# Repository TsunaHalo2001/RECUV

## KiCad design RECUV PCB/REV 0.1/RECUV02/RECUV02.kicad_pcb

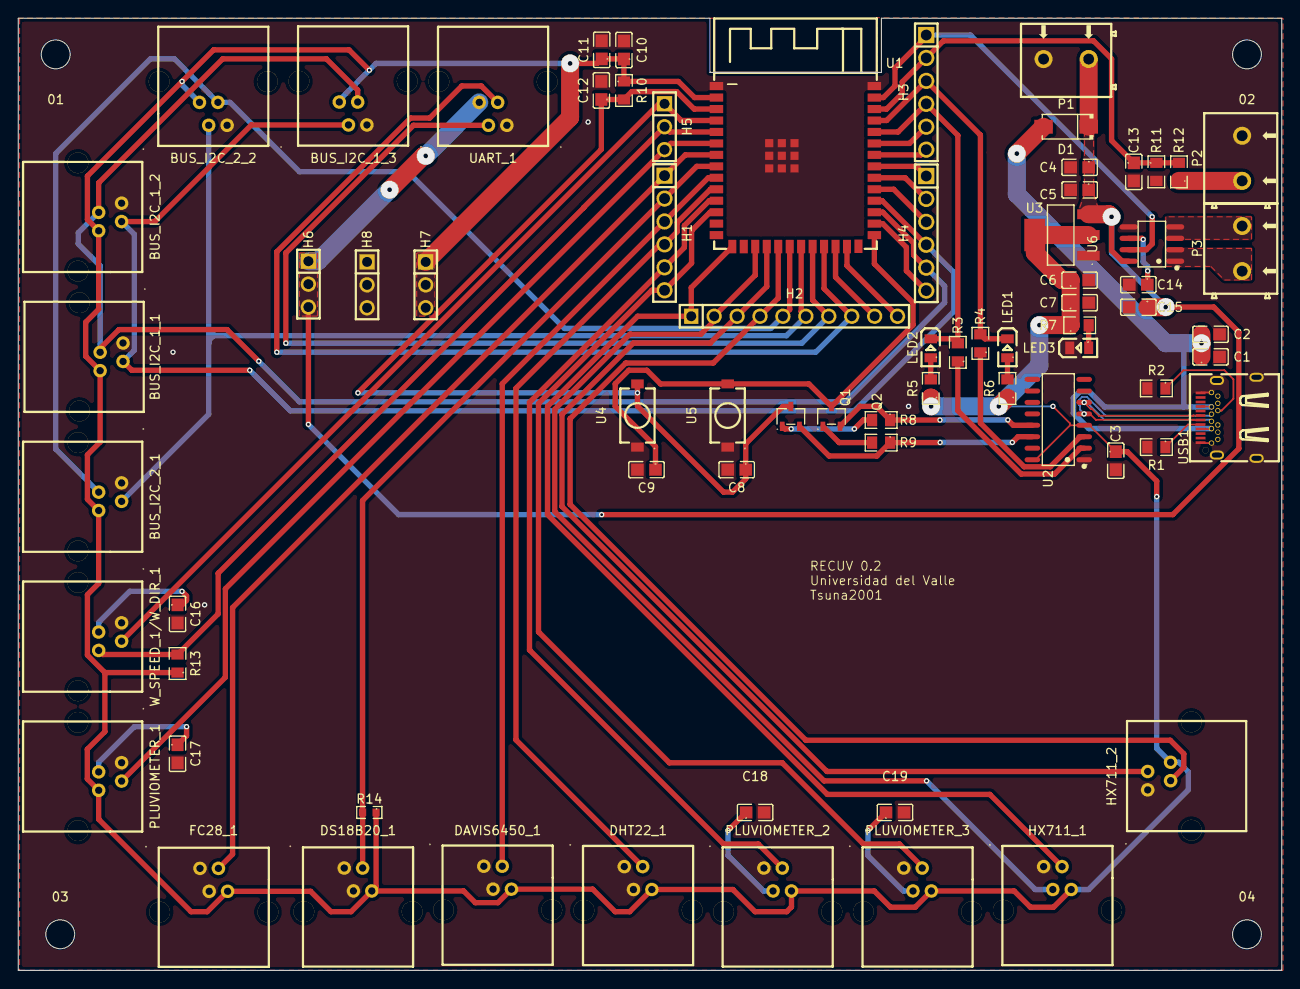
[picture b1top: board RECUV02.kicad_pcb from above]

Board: 2 copper layers, 140.0 x 105.5 mm, 77 parts (0 on the bottom side), 58 nets.

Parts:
01, 02, 03, 04: MountingHole_3.2mm_M3
BUS_I2C_1_1, BUS_I2C_2_1: TSL2591; RJ11-TH_PCB-6P4C-90
BUS_I2C_1_2: PRES_ATMOS; RJ11-TH_PCB-6P4C-90
BUS_I2C_1_3, BUS_I2C_2_2: EXTENDER; RJ11-TH_PCB-6P4C-90
C1, C5, C6, C10: 10u; C0805
C2, C3, C4, C7, C8, C9, C11, C13, C15, C16, C17, C18, C19: 100n; C0805
C12: 1u; C0805
C14: 1n; C0805
D1: SS54_C22452; SMA_L4.4-W2.8-LS5.4-R-RD
DAVIS6450_1: SOLAR_RADIATION; RJ11-TH_PCB-6P4C-90
DHT22_1: AIR_HUMIDITY/AIR_TEMPERATURE; RJ11-TH_PCB-6P4C-90
DS18B20_1: TEMP_SOIL; RJ11-TH_PCB-6P4C-90
FC28_1: HUMIDITY_SOIL; RJ11-TH_PCB-6P4C-90
H1: LEFT_ROW_2; HDR-TH_6P-P2.54-V-M-1
H2: LOW_ROW; HDR-TH_10P-P2.54-V-M-1
H3: RIGHT_ROW_1; HDR-TH_6P-P2.54-V-M-1
H4: RIGHT_ROW_2; HDR-TH_6P-P2.54-V-M-1
H5: LEFT_ROW_1; HDR-TH_3P-P2.54-V-M
H6: 5V_ROW; HDR-TH_3P-P2.54-V-M
H7: 3V3_ROW; HDR-TH_3P-P2.54-V-M
H8: GND_ROW; HDR-TH_3P-P2.54-V-M
HX711_1, HX711_2: NET_WEIGHT; RJ11-TH_PCB-6P4C-90
LED1: Green; LED0805-R-RD
LED2: Blue; LED0805-R-RD
LED3: Red; LED0805-R-RD
P1: VEXT; CONN-TH_2P-P5.00_CPC3703CTR
P2: VOLTAGE; CONN-TH_2P-P5.00_CPC3703CTR
P3: CURRENT; CONN-TH_2P-P5.00_CPC3703CTR
PLUVIOMETER_1, PLUVIOMETER_2, PLUVIOMETER_3: PLUVIOMETER; RJ11-TH_PCB-6P4C-90
Q1, Q2: MMBT2222ALT1; SOT-23-3_L3.0-W1.7-P0.95-LS2.9-BR
R1, R2: 5.1k; R0805
R3, R4: 1k; R0805
R5, R6, R7: 470; R0805
R8, R9, R10, R11, R13: 10k; R0805
R12: 100k; R0805
R14: 2.2k; R0603
U1: ESP32-S3-WROOM-1; WIRELM-SMD_ESP32-S3-WROOM-1
U2: CH340C; SOP-16_L10.0-W3.9-P1.27-LS6.0-BL
U3: A1117-3.3; SOT-223-3_L6.5-W3.4-P2.30-LS7.0-BR-1
U4: RESET; SW-SMD_KSR213GLFG
U5: BOOT; SW-SMD_KSR213GLFG
U6: ACS712ELCTR-20A-T; SOIC-8_L4.9-W3.9-P1.27-LS6.0-BL
UART_1: COMMUNICATION; RJ11-TH_PCB-6P4C-90
USB1: USB-306; USB-TYPE-C-TH_USB-306-1
W_SPEED_1/W_DIR_1: WIND; RJ11-TH_PCB-6P4C-90

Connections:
3V3: BUS_I2C_1_1.4, BUS_I2C_1_2.4, BUS_I2C_1_3.4, BUS_I2C_2_1.4, BUS_I2C_2_2.4, C3.1, C6.1, C7.1, C10.1, C11.1, DAVIS6450_1.4, DHT22_1.4, DS18B20_1.4, FC28_1.4, H7.1, H7.2, H7.3, HX711_1.4, HX711_2.4, PLUVIOMETER_1.4, PLUVIOMETER_2.4, PLUVIOMETER_3.4, R5.1, R6.1, R7.1, R10.1, R13.1, R14.1, U1.2 (3V3), U2.4 (V3), U2.16 (VCC), U3.2 (VOUT)
+5V: C4.1, C5.1, C15.1, D1.2 (K), H6.1, H6.2, H6.3, P1.1, U3.3 (VIN), U6.8 (VCC), UART_1.4
CHIP_PU: C8.1, C12.1, Q1.3 (C), R10.2, U1.3 (EN), U4.2
DTR: Q2.2 (E), R8.1, U2.13 (~DTR)
GND: BUS_I2C_1_1.1, BUS_I2C_1_2.1, BUS_I2C_1_3.1, BUS_I2C_2_1.1, BUS_I2C_2_2.1, C1.2, C2.2, C3.2, C4.2, C5.2, C6.2, C7.2, C8.2, C9.2, C10.2, C11.2, C12.2, C13.2, C14.2, C15.2, C16.2, C17.2, C18.2, C19.2, DAVIS6450_1.1, DAVIS6450_1.2, DHT22_1.1, DHT22_1.2, DS18B20_1.1, DS18B20_1.2, FC28_1.1, FC28_1.2, H8.1, H8.2, H8.3, HX711_1.1, HX711_2.1, LED3.2 (K), P1.2, P2.2, PLUVIOMETER_1.1, PLUVIOMETER_2.1, PLUVIOMETER_3.1, R1.2, R2.2, R11.2, U1.1 (GND), U1.40 (GND), U1.41 (GND), U2.1 (GND), U3.1 (ADJ/GND), U4.1, U5.1, U6.5 (GND), UART_1.1, USB1.25 (EH), USB1.A1 (GND), USB1.A12 (GND), USB1.B1 (GND), USB1.B12 (GND), W_SPEED_1/W_DIR_1.1
GPIO00: C9.1, Q2.3 (C), U1.27 (IO0), U5.2
GPIO01: H3.1, U1.39 (IO1), U6.7 (VIOUT)
GPIO02: C13.1, H3.2, R11.1, R12.2, U1.38 (IO2)
GPIO03: H2.1, HX711_1.3, U1.15 (IO3)
GPIO04: H5.1, U1.4 (IO4), W_SPEED_1/W_DIR_1.3
GPIO05: H5.2, R13.2, U1.5 (IO5), W_SPEED_1/W_DIR_1.4
GPIO06: H5.3, PLUVIOMETER_1.3, U1.6 (IO6)
GPIO07: FC28_1.3, H1.1, U1.7 (IO7)
GPIO08: H1.6, PLUVIOMETER_3.3, U1.12 (IO8)
GPIO09: H2.2, HX711_1.2, U1.17 (IO9)
GPIO10: H2.3, HX711_2.3, U1.18 (IO10)
GPIO11: H2.4, HX711_2.2, U1.19 (IO11)
GPIO12: BUS_I2C_2_1.2, BUS_I2C_2_2.2, H2.5, U1.20 (IO12)
GPIO13: BUS_I2C_2_1.3, BUS_I2C_2_2.3, H2.6, U1.21 (IO13)
GPIO14: H2.7, U1.22 (IO14), UART_1.3
GPIO15: DS18B20_1.3, H1.2, R14.2, U1.8 (IO15)
GPIO16: DAVIS6450_1.3, H1.3, U1.9 (IO16)
GPIO17: DHT22_1.3, H1.4, U1.10 (IO17)
GPIO18: H1.5, PLUVIOMETER_2.3, U1.11 (IO18)
GPIO21: H2.8, U1.23 (IO21), UART_1.2
GPIO35: H4.6, U1.28 (IO35)
GPIO36: BUS_I2C_1_1.2, BUS_I2C_1_2.2, BUS_I2C_1_3.2, H4.5, U1.29 (IO36)
GPIO37: BUS_I2C_1_1.3, BUS_I2C_1_2.3, BUS_I2C_1_3.3, H4.4, U1.30 (IO37)
GPIO38: H4.3, U1.31 (IO38)
GPIO39: H4.2, U1.32 (IO39)
GPIO40: H4.1, U1.33 (IO40)
GPIO41: H3.6, U1.34 (IO41)
GPIO42: H3.5, U1.35 (IO42)
GPIO47: H2.9, U1.24 (IO47)
GPIO48: H2.10, U1.25 (IO48)
unnamed: C16.1, W_SPEED_1/W_DIR_1.2
unnamed: C17.1, PLUVIOMETER_1.2
unnamed: C18.1, PLUVIOMETER_2.2
unnamed: C19.1, PLUVIOMETER_3.2
unnamed: LED1.1 (A), R6.2
unnamed: LED2.1 (A), R5.2
unnamed: LED3.1 (A), R7.2
unnamed: P3.1, U6.1 (IP+), U6.2 (IP+)
unnamed: P3.2, U6.3 (IP-), U6.4 (IP-)
unnamed: Q1.1 (B), R8.2
unnamed: Q2.1 (B), R9.2
unnamed: R4.1, U2.3 (RXD)
unnamed: R3.1, U2.2 (TXD)
unnamed: C14.1, U6.6 (FILTER)
unnamed: R1.1, USB1.A5 (CC1)
unnamed: R2.1, USB1.B5 (CC2)
RTS: Q1.2 (E), R9.1, U2.14 (~RTS)
U0RXD: H3.4, LED2.2 (K), R3.2, U1.36 (RXD0)
U0TXD: H3.3, LED1.2 (K), R4.2, U1.37 (TXD0)
UD+: U2.5 (D+), USB1.A6 (DP1), USB1.B6 (DP2)
UD-: U2.6 (D-), USB1.A7 (DN1), USB1.B7 (DN2)
VBAT: P2.1, R12.1
VBUS: C1.1, C2.1, D1.1 (A), USB1.A4 (VBUS), USB1.A9 (VBUS), USB1.B4 (VBUS), USB1.B9 (VBUS)

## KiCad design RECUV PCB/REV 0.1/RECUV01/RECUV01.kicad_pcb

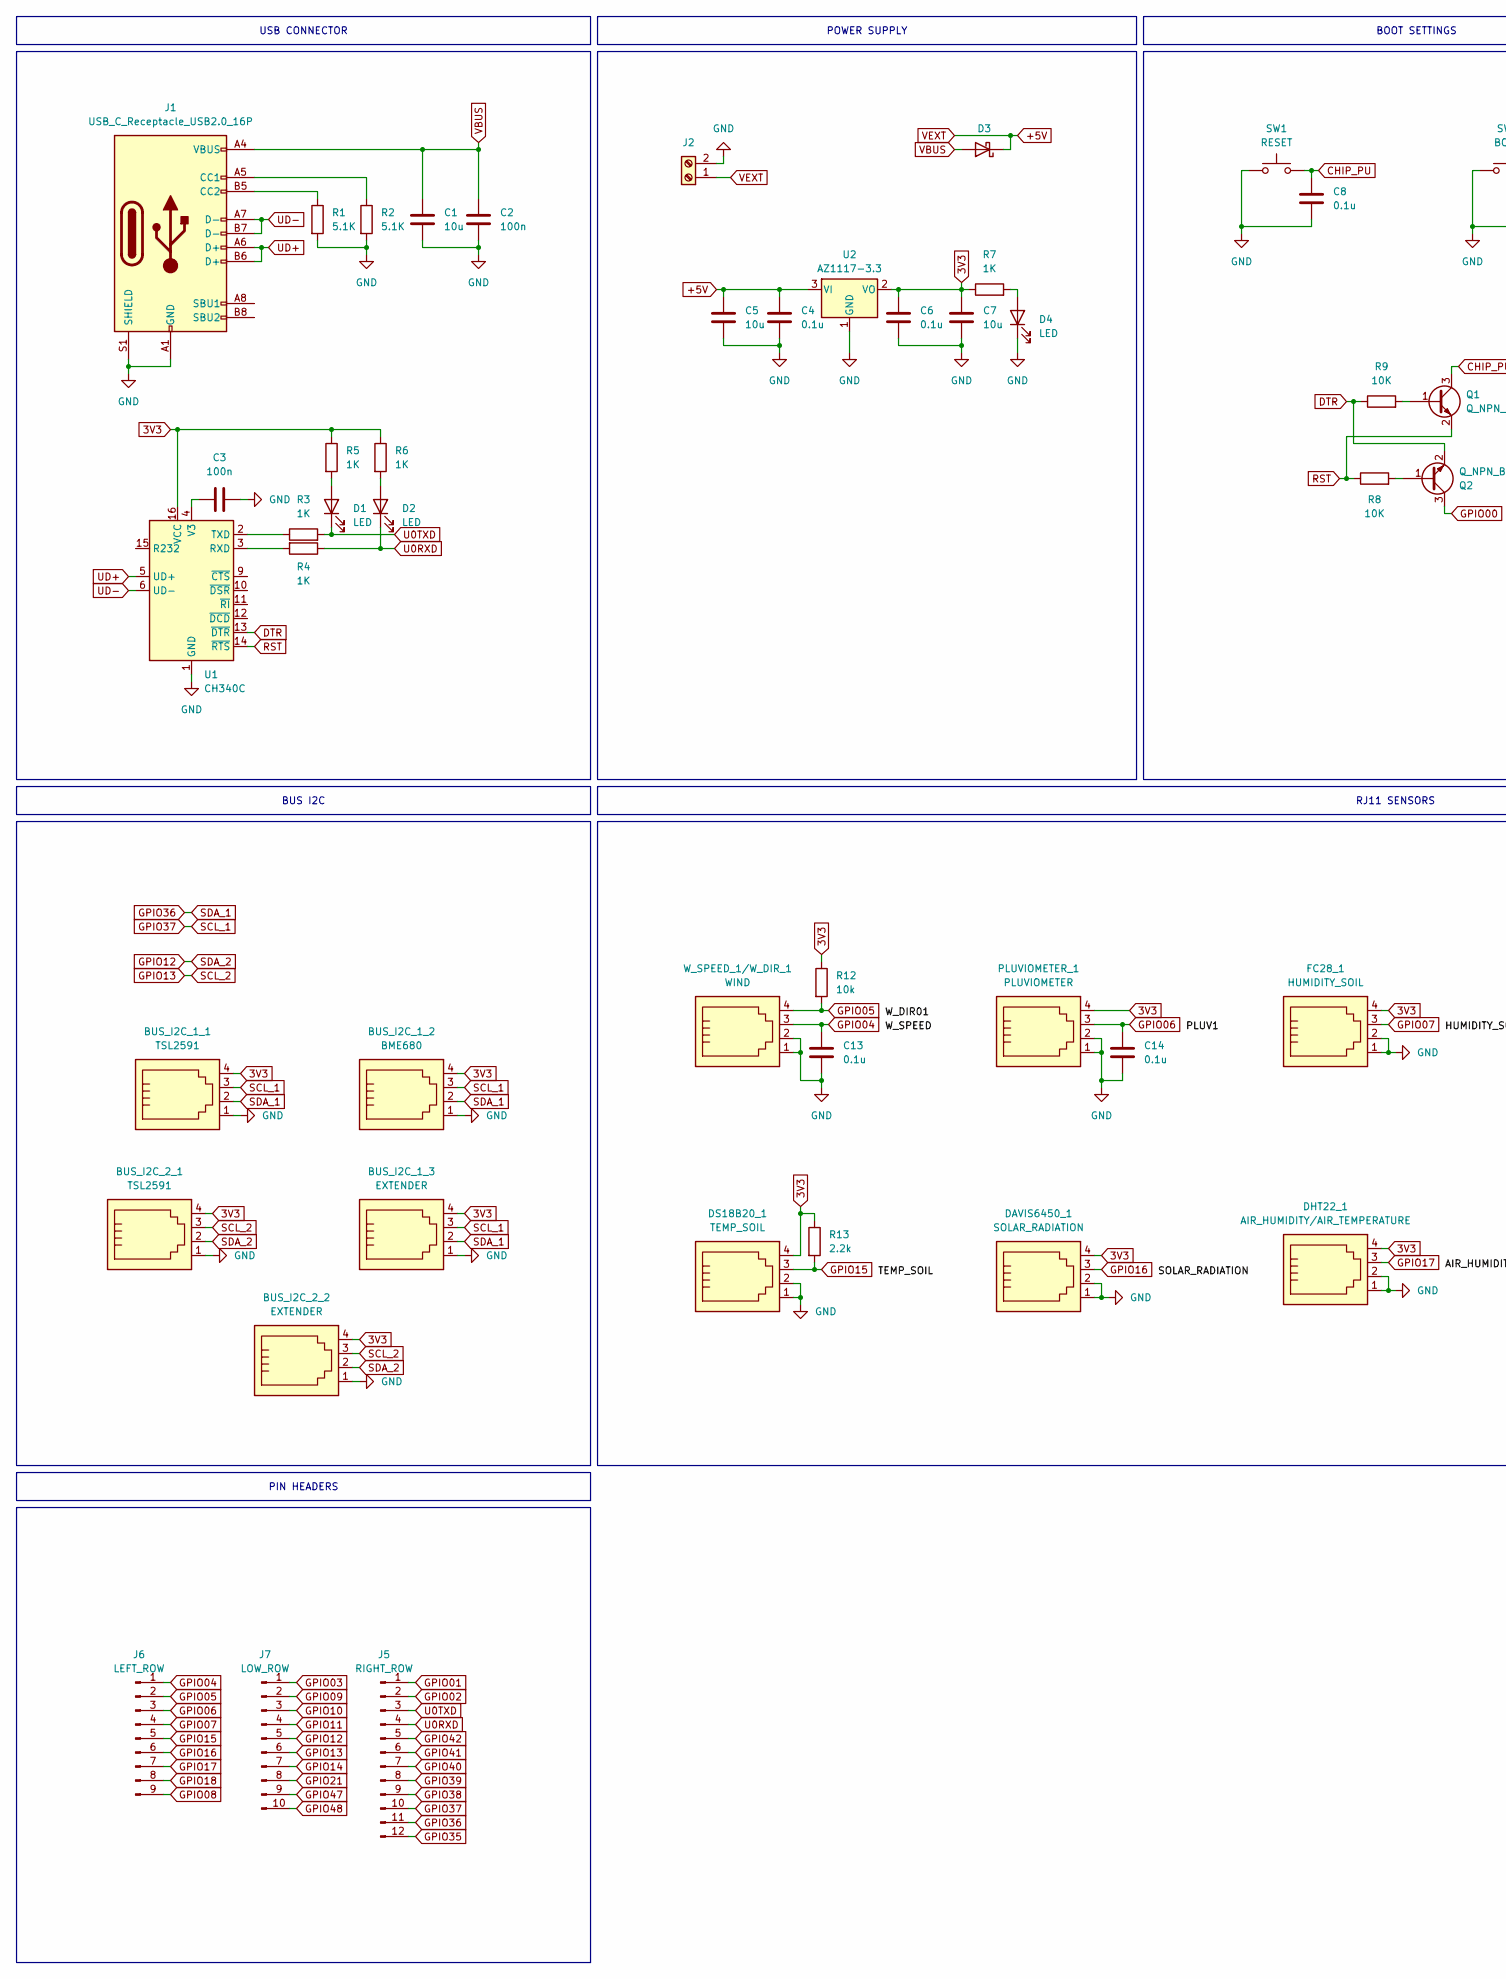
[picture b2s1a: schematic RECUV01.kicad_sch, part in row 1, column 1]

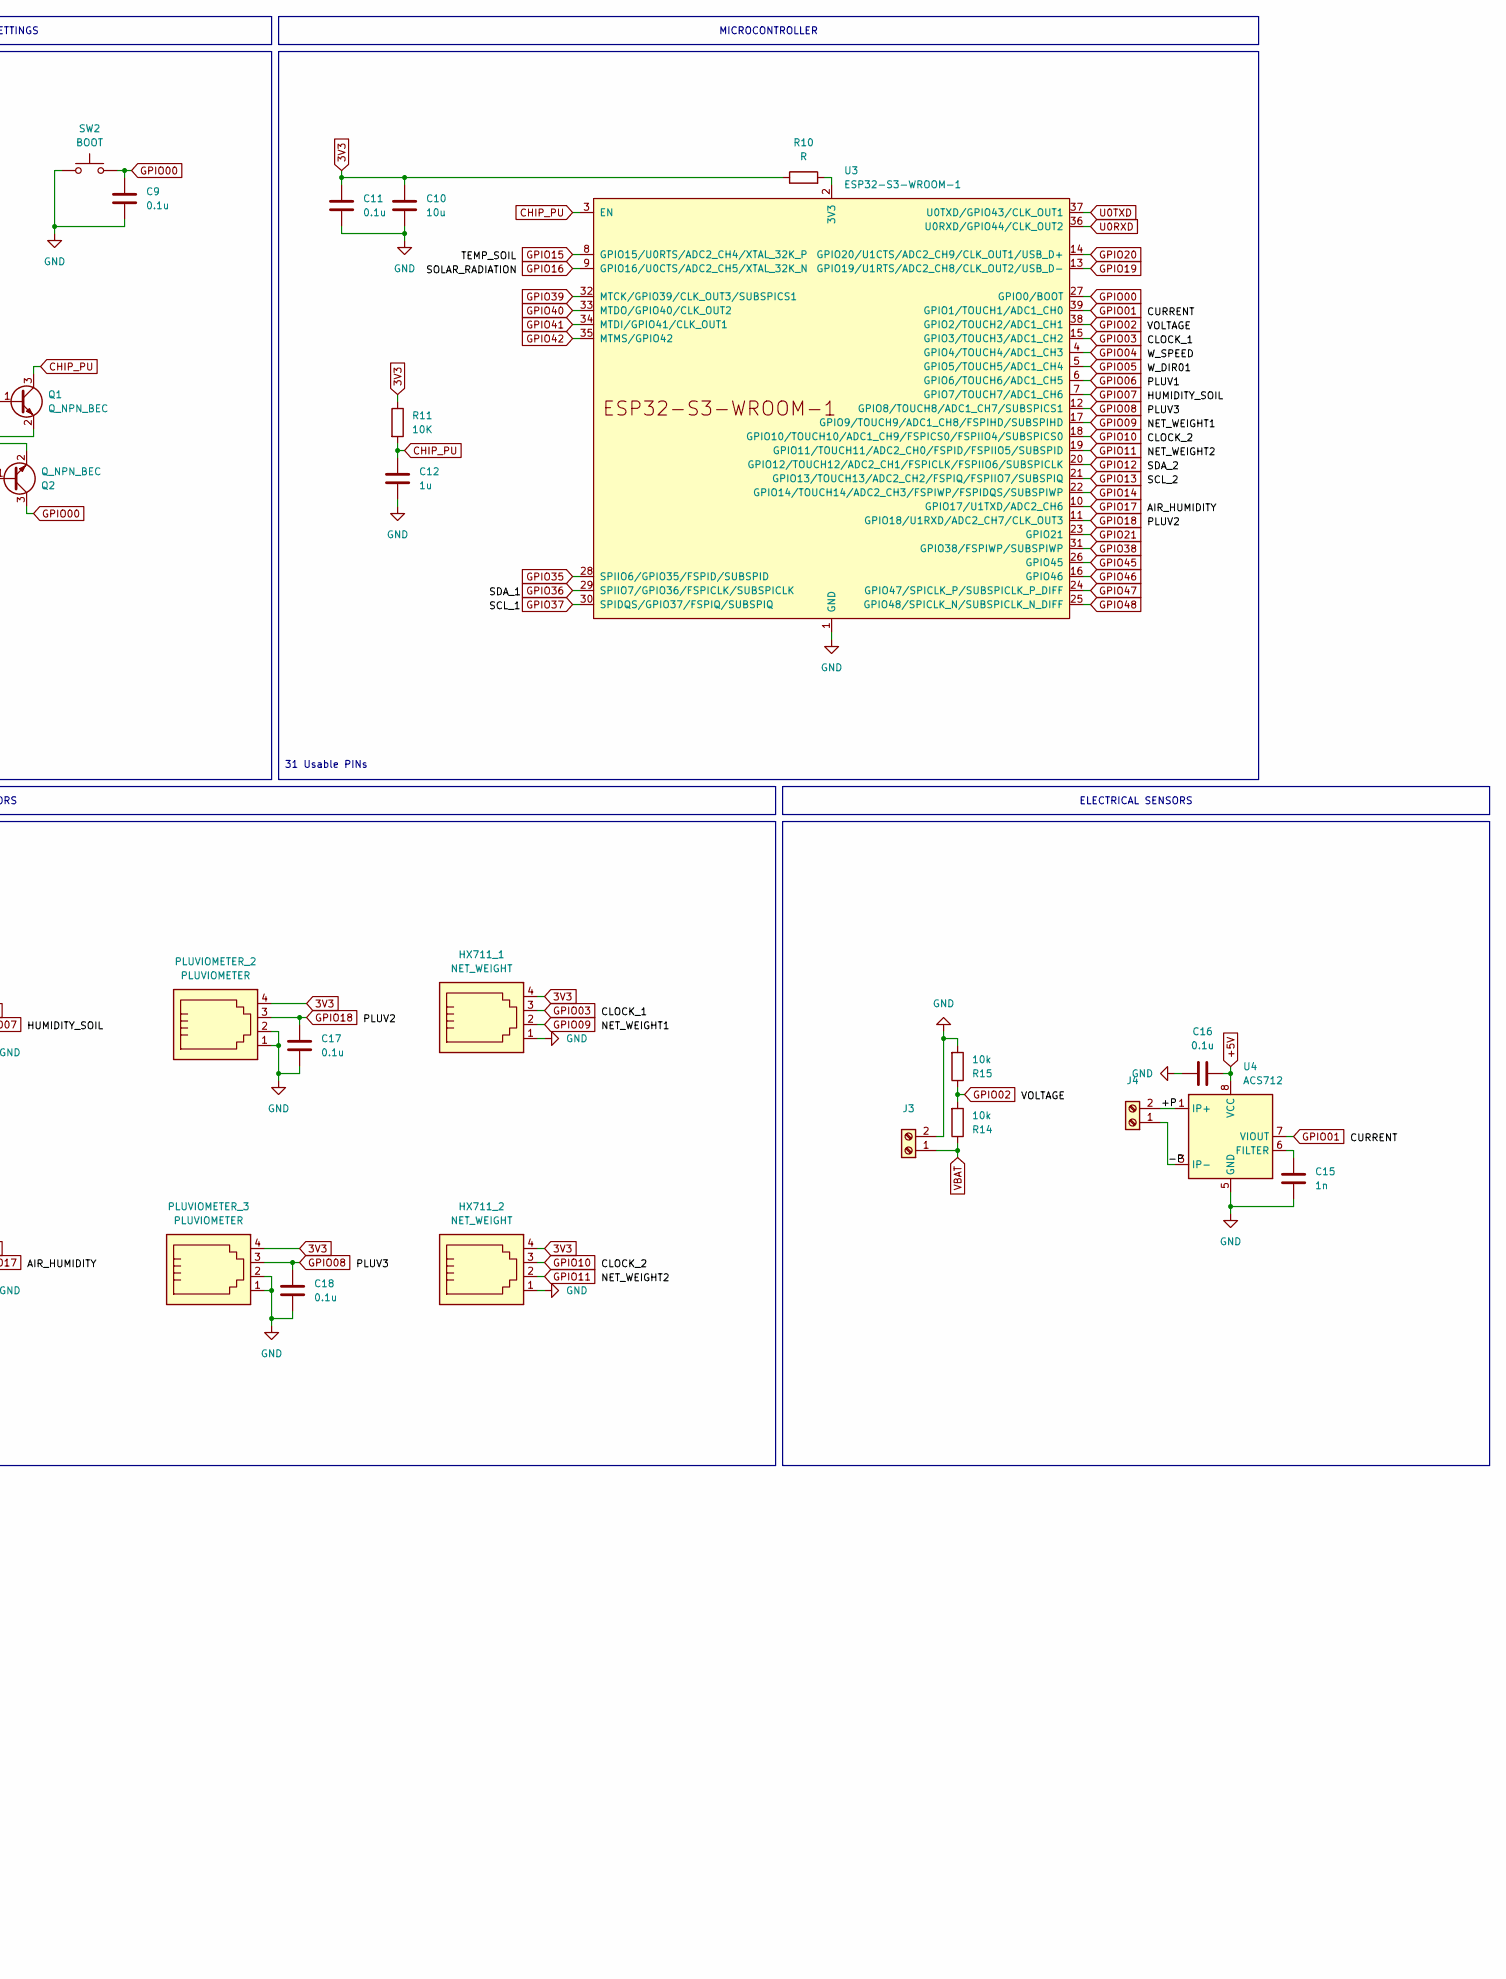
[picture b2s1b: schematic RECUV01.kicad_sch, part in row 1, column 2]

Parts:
BUS_I2C_1_1, BUS_I2C_2_1: TSL2591; RJ9_Evercom_5301-440xxx_Horizontal
BUS_I2C_1_2: BME680; RJ9_Evercom_5301-440xxx_Horizontal
BUS_I2C_1_3, BUS_I2C_2_2: EXTENDER; RJ9_Evercom_5301-440xxx_Horizontal
C1, C5, C7, C10: 10u; C_0805_2012Metric
C2, C3: 100n; C_0805_2012Metric
C4, C6, C8, C9, C11, C13, C14, C16, C17, C18: 0.1u; C_0805_2012Metric
C12: 1u; C_0805_2012Metric
C15: 1n; C_0805_2012Metric
D1, D2, D4: LED; LED_0805_2012Metric
D3: D_Schottky; D_SMA
DAVIS6450_1: SOLAR_RADIATION; RJ9_Evercom_5301-440xxx_Horizontal
DHT22_1: AIR_HUMIDITY/AIR_TEMPERATURE; RJ9_Evercom_5301-440xxx_Horizontal
DS18B20_1: TEMP_SOIL; RJ9_Evercom_5301-440xxx_Horizontal
FC28_1: HUMIDITY_SOIL; RJ9_Evercom_5301-440xxx_Horizontal
HX711_1, HX711_2: NET_WEIGHT; RJ9_Evercom_5301-440xxx_Horizontal
J1: USB_C_Receptacle_USB2.0_16P; USB_C_Receptacle_XKB_U262-16XN-4BVC11
J2: Screw_Terminal_01x02; TerminalBlock_Altech_AK300-2_P5.00mm
J3, J4: TerminalBlock_Altech_AK300-2_P5.00mm
J5: RIGHT_ROW; PinHeader_1x12_P2.54mm_Vertical
J6: LEFT_ROW; PinHeader_1x09_P2.54mm_Vertical
J7: LOW_ROW; PinHeader_1x10_P2.54mm_Vertical
PLUVIOMETER_1, PLUVIOMETER_2, PLUVIOMETER_3: PLUVIOMETER; RJ9_Evercom_5301-440xxx_Horizontal
Q1, Q2: Q_NPN_BEC; SOT-23-3
R1, R2: 5.1K; R_0805_2012Metric
R3, R4, R5, R6, R7: 1K; R_0805_2012Metric
R8, R9, R11: 10K; R_0805_2012Metric
R10: R; R_0805_2012Metric
R12, R14, R15: 10k; R_0805_2012Metric
R13: 2.2k; R_0805_2012Metric
SW1: RESET; SW_Tactile_SPST_NO_Straight_CK_PTS636Sx25SMTRLFS
SW2: BOOT; SW_Tactile_SPST_NO_Straight_CK_PTS636Sx25SMTRLFS
U1: CH340C; SOIC-16_3.9x9.9mm_P1.27mm
U2: AZ1117-3.3; SOT-223-3_TabPin2
U3: ESP32-S3-WROOM-1
U4: ACS712; SOIC-8_3.9x4.9mm_P1.27mm
W_SPEED_1/W_DIR_1: WIND; RJ9_Evercom_5301-440xxx_Horizontal

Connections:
3V3: BUS_I2C_1_1.4, BUS_I2C_1_2.4, BUS_I2C_1_3.4, BUS_I2C_2_1.4, BUS_I2C_2_2.4, C6.1, C7.1, C10.1, C11.1, DAVIS6450_1.4, DHT22_1.4, DS18B20_1.4, FC28_1.4, HX711_1.4, HX711_2.4, PLUVIOMETER_1.4, PLUVIOMETER_2.4, PLUVIOMETER_3.4, R5.1, R6.1, R7.1, R10.1, R11.1, R12.1, R13.1, U1.16 (VCC), U2.2 (VO)
+5V: C4.1, C5.1, C16.2, D3.1 (K), J2.1, U2.3 (VI), U4.8 (VCC)
/+P: J4.2, U4.1 (IP+), U4.2 (IP+)
/-P: J4.1, U4.3 (IP-), U4.4 (IP-)
CHIP_PU: C8.1, C12.1, Q1.3 (C), R11.2, SW1.2, U3.3 (EN)
DTR: Q2.2 (E), R9.1, U1.13 (~DTR)
GND: BUS_I2C_1_1.1, BUS_I2C_1_2.1, BUS_I2C_1_3.1, BUS_I2C_2_1.1, BUS_I2C_2_2.1, C1.2, C2.2, C3.2, C4.2, C5.2, C6.2, C7.2, C8.2, C9.2, C10.2, C11.2, C12.2, C13.2, C14.2, C15.2, C16.1, C17.2, C18.2, D4.1 (K), DAVIS6450_1.1, DAVIS6450_1.2, DHT22_1.1, DHT22_1.2, DS18B20_1.1, DS18B20_1.2, FC28_1.1, FC28_1.2, HX711_1.1, HX711_2.1, J1.A1 (GND), J1.A12 (GND), J1.B1 (GND), J1.B12 (GND), J1.S1 (SHIELD), J2.2, J3.2, PLUVIOMETER_1.1, PLUVIOMETER_1.2, PLUVIOMETER_2.1, PLUVIOMETER_2.2, PLUVIOMETER_3.1, PLUVIOMETER_3.2, R1.2, R2.2, R15.2, SW1.1, SW2.1, U1.1 (GND), U2.1 (GND), U3.1 (GND), U3.40 (GND), U3.41 (GND), U4.5 (GND), W_SPEED_1/W_DIR_1.1, W_SPEED_1/W_DIR_1.2
GPIO00: C9.1, Q2.3 (C), SW2.2, U3.27 (GPIO0/BOOT)
GPIO01: J5.1, U3.39 (GPIO1/TOUCH1/ADC1_CH0), U4.7 (VIOUT)
GPIO02: J5.2, R14.2, R15.1, U3.38 (GPIO2/TOUCH2/ADC1_CH1)
GPIO03: HX711_1.3, J7.1, U3.15 (GPIO3/TOUCH3/ADC1_CH2)
GPIO04: C13.1, J6.1, U3.4 (GPIO4/TOUCH4/ADC1_CH3), W_SPEED_1/W_DIR_1.3
GPIO05: J6.2, R12.2, U3.5 (GPIO5/TOUCH5/ADC1_CH4), W_SPEED_1/W_DIR_1.4
GPIO06: C14.1, J6.3, PLUVIOMETER_1.3, U3.6 (GPIO6/TOUCH6/ADC1_CH5)
GPIO07: FC28_1.3, J6.4, U3.7 (GPIO7/TOUCH7/ADC1_CH6)
GPIO08: C18.1, J6.9, PLUVIOMETER_3.3, U3.12 (GPIO8/TOUCH8/ADC1_CH7/SUBSPICS1)
GPIO09: HX711_1.2, J7.2, U3.17 (GPIO9/TOUCH9/ADC1_CH8/FSPIHD/SUBSPIHD)
GPIO10: HX711_2.3, J7.3, U3.18 (GPIO10/TOUCH10/ADC1_CH9/FSPICS0/FSPIIO4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)
GPIO11: HX711_2.2, J7.4, U3.19 (GPIO11/TOUCH11/ADC2_CH0/FSPID/FSPIIO5/S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)
GPIO12: BUS_I2C_2_1.2, BUS_I2C_2_2.2, J7.5, U3.20 (GPIO12/TOUCH12/ADC2_CH1/FSPICLK/FSPIIO6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)
GPIO13: BUS_I2C_2_1.3, BUS_I2C_2_2.3, J7.6, U3.21 (GPIO13/TOUCH13/ADC2_CH2/FSPIQ/FSPIIO7/S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)
GPIO14: J7.7, U3.22 (GPIO14/TOUCH14/ADC2_CH3/FSPIWP/FSPIDQS/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)
GPIO15: DS18B20_1.3, J6.5, R13.2, U3.8 (GPIO15/U0RTS/ADC2_CH4/XTAL_32K_P)
GPIO16: DAVIS6450_1.3, J6.6, U3.9 (GPIO16/U0CTS/ADC2_CH5/XTAL_32K_N)
GPIO17: DHT22_1.3, J6.7, U3.10 (GPIO17/U1TXD/ADC2_CH6)
GPIO18: C17.1, J6.8, PLUVIOMETER_2.3, U3.11 (GPIO18/U1RXD/ADC2_CH7/CLK_OUT3)
GPIO19: U3.13 (GPIO19/U1RTS/ADC2_CH8/CLK_OUT2/USB_D-)
GPIO20: U3.14 (GPIO20/U1CTS/ADC2_CH9/CLK_OUT1/USB_D+)
GPIO21: J7.8, U3.23 (GPIO21)
GPIO35: J5.12, U3.28 (SPIIO6/GPIO35/FSPID/SUBSPID)
GPIO36: BUS_I2C_1_1.2, BUS_I2C_1_2.2, BUS_I2C_1_3.2, J5.11, U3.29 (SPIIO7/GPIO36/FSPICLK/SUBSPICLK)
GPIO37: BUS_I2C_1_1.3, BUS_I2C_1_2.3, BUS_I2C_1_3.3, J5.10, U3.30 (SPIDQS/GPIO37/FSPIQ/SUBSPIQ)
GPIO38: J5.9, U3.31 (GPIO38/FSPIWP/SUBSPIWP)
GPIO39: J5.8, U3.32 (MTCK/GPIO39/CLK_OUT3/SUBSPICS1)
GPIO40: J5.7, U3.33 (MTDO/GPIO40/CLK_OUT2)
GPIO41: J5.6, U3.34 (MTDI/GPIO41/CLK_OUT1)
GPIO42: J5.5, U3.35 (MTMS/GPIO42)
GPIO45: U3.26 (GPIO45)
GPIO46: U3.16 (GPIO46)
GPIO47: J7.9, U3.24 (GPIO47/SPICLK_P/SUBSPICLK_P_DIFF)
GPIO48: J7.10, U3.25 (GPIO48/SPICLK_N/SUBSPICLK_N_DIFF)
unnamed: D1.2 (A), R5.2
unnamed: D2.2 (A), R6.2
unnamed: D4.2 (A), R7.2
unnamed: J1.A5 (CC1), R2.1
unnamed: J1.B5 (CC2), R1.1
unnamed: Q1.1 (B), R9.2
unnamed: Q2.1 (B), R8.2
unnamed: R4.2, U1.3 (RXD)
unnamed: R3.1, U1.2 (TXD)
unnamed: C3.1, U1.4 (V3)
unnamed: R10.2, U3.2 (3V3)
unnamed: C15.1, U4.6 (FILTER)
RST: Q1.2 (E), R8.1, U1.14 (~RTS)
U0RXD: D2.1 (K), J5.4, R4.1, U3.36 (U0RXD/GPIO44/CLK_OUT2)
U0TXD: D1.1 (K), J5.3, R3.2, U3.37 (U0TXD/GPIO43/CLK_OUT1)
UD+: J1.A6 (D+), J1.B6 (D+), U1.5 (UD+)
UD-: J1.A7 (D-), J1.B7 (D-), U1.6 (UD-)
VBAT: J3.1, R14.1
VBUS: C1.1, C2.1, D3.2 (A), J1.A4 (VBUS), J1.A9 (VBUS), J1.B4 (VBUS), J1.B9 (VBUS)

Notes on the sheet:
BOOT SETTINGS
USB CONNECTOR
RJ11 SENSORS
ELECTRICAL SENSORS
PIN HEADERS
BUS I2C
MICROCONTROLLER
POWER SUPPLY
31 Usable PINs

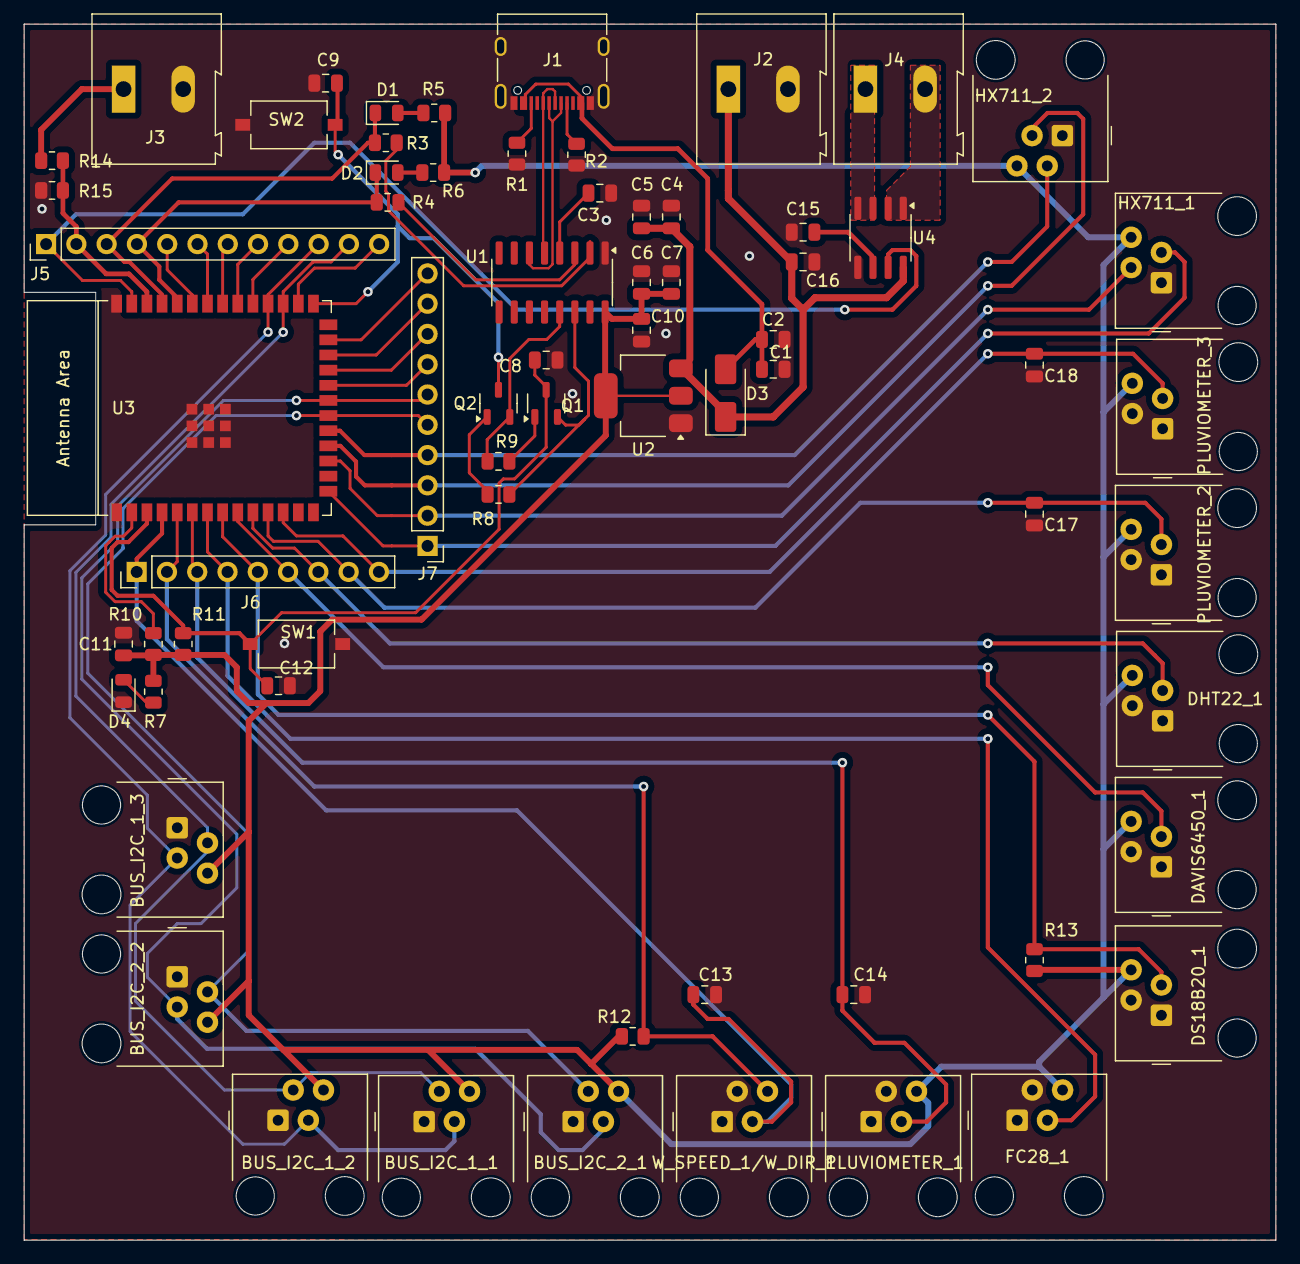
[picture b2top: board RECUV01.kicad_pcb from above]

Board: 2 copper layers, 105.0 x 102.0 mm, 67 parts (0 on the bottom side), 56 nets.

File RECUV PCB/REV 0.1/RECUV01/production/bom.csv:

Designator,Footprint,Quantity,Value,LCSC Part #
"BUS_I2C_1_1, BUS_I2C_2_1",RJ9_Evercom_5301-440xxx_Horizontal,2,TSL2591,
BUS_I2C_1_2,RJ9_Evercom_5301-440xxx_Horizontal,1,BME680,
"BUS_I2C_1_3, BUS_I2C_2_2",RJ9_Evercom_5301-440xxx_Horizontal,2,EXTENDER,
"C1, C10, C5, C7",0805,4,10u,
"C11, C13, C14, C16, C17, C18, C4, C6, C8, C9",0805,10,0.1u,
C12,0805,1,1u,
C15,0805,1,1n,
"C2, C3",0805,2,100n,
"D1, D2, D4",0805,3,LED,
D3,D_SMA,1,D_Schottky,
DAVIS6450_1,RJ9_Evercom_5301-440xxx_Horizontal,1,SOLAR_RADIATION,
DHT22_1,RJ9_Evercom_5301-440xxx_Horizontal,1,AIR_HUMIDITY/AIR_TEMPERATURE,
DS18B20_1,RJ9_Evercom_5301-440xxx_Horizontal,1,TEMP_SOIL,
FC28_1,RJ9_Evercom_5301-440xxx_Horizontal,1,HUMIDITY_SOIL,
"HX711_1, HX711_2",RJ9_Evercom_5301-440xxx_Horizontal,2,NET_WEIGHT,
J1,USB_C_Receptacle_XKB_U262-16XN-4BVC11,1,USB,
J2,TerminalBlock_Altech_AK300-2_P5.00mm,1,VEXT,
J3,TerminalBlock_Altech_AK300-2_P5.00mm,1,VOLTAGE,
J4,TerminalBlock_Altech_AK300-2_P5.00mm,1,CURRENT,
J5,PinHeader_1x12_P2.54mm_Vertical,1,RIGHT_ROW,
J6,PinHeader_1x09_P2.54mm_Vertical,1,LEFT_ROW,
J7,PinHeader_1x10_P2.54mm_Vertical,1,LOW_ROW,
"PLUVIOMETER_1, PLUVIOMETER_2, PLUVIOMETER_3",RJ9_Evercom_5301-440xxx_Horizontal,3,PLUVIOMETER,
"Q1, Q2",SOT-23-3,2,Q_NPN_BEC,
"R1, R2",0805,2,5.1K,
R10,0805,1,R,
"R11, R12, R14, R15, R8, R9",0805,6,10K,
R13,0805,1,2.2k,
"R3, R4, R5, R6, R7",0805,5,1K,
SW1,SW_Tactile_SPST_NO_Straight_CK_PTS636Sx25SMTRLFS,1,RESET,
SW2,SW_Tactile_SPST_NO_Straight_CK_PTS636Sx25SMTRLFS,1,BOOT,
U1,SOIC-16_3.9x9.9mm_P1.27mm,1,CH340C,
U2,SOT-223-3_TabPin2,1,AZ1117-3.3,
U3,ESP32-S3-WROOM-1,1,ESP32-S3-WROOM-1,
U4,SOIC-8_3.9x4.9mm_P1.27mm,1,ACS712,
W_SPEED_1/W_DIR_1,RJ9_Evercom_5301-440xxx_Horizontal,1,WIND,

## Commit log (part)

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2024-07-11 Added RECUV 1 and BMP180 lib
2024-07-12 Added HCSR04 lib
2024-07-16 16julio2024
2024-07-18 17-07-2024
2024-07-18 Added DS1302 lib
2024-07-18 18-07-2024, UPDATE RECUV2
2024-07-18 added docs
2024-07-19 Updated RECUV doc
2024-07-19 updated doc
2024-07-19 Added trampa, pending galga and extinc
2024-07-22 Added trampa reception
2024-07-24 added missing
2024-07-25 25-07-2024
2024-07-26 removed 2 traps added variables, updated doc
2024-07-26 Reordered folders
2024-07-26 updated to peso values
2024-07-26 finished Trampa and RECUV 2
2024-07-26 simplified RECUV2 ESP32, added upy version
2024-07-26 julio-26-2024
2024-07-31 added bmp180 i2c to esp32 and corrected code
2024-07-31 prepared code and added macs
2024-08-01 corrected esp, added visual on trama
2024-08-01 Added better flags reduced time
2024-08-01 correction
2024-08-08 Updated recuvs
2024-08-08 updated recuv 3
2024-08-08 updated pins
2024-08-08 RECUV 3 finished
2024-08-18 #define DirVelPin A15
2024-08-19 Corrected comunicador
2025-02-10 Añadida rutina para reiniciar la ESP32 con intervalos regulares para evitar la detencion del programa
2025-02-22 Create restrictionssh.yml
    added ssh
2025-05-16 PCB files
2025-07-04 Add maintenance information for K18 and Tocota recovery stations
2025-07-05 Update maintenance guide with detailed steps for BMP180 and ESP32 connections, and add instructions for adding new data server addresses.
2025-07-10 Add initial Gerber job file for RECUV01 PCB design
    - Created RECUV01-job.gbrjob file with project specifications
    - Included header information with generation software details
    - Defined general specifications such as project ID, size, layer number, and board thickness
    - Specified design rules for pad and track spacing
    - Listed file attributes for copper layers, solder paste, silkscreen, solder mask, and edge cuts
    - Documented material stackup including types and thicknesses for each layer
2026-01-13 Se corrigio TX y RX del CH340 en esquematico
    TODO:
    Corregirlo en PCB
2026-01-16 Added all changes for beta, work rtc and wifi, todo everything and ask for rtc online
2026-01-18 added rtc online and sen15901, todo the rest
2026-01-22 TODO soil and communication
2026-01-22 TODO humidity and com
2026-01-23 TODO communication
2026-01-23 added JSON
2026-01-23 TODO emergency sends
2026-01-23 Actualizar variables.json versión 2
2026-01-23 TODO check wind interrupt, voltage and current
2026-01-24 Actualizar variables.json 3
2026-01-24 Actualizar variables.json 4
2026-01-26 Finished code, TODO comments and some refactoring for readability
2026-01-27 Actualizar variables.json 5
2026-01-28 added k18 network and corrected davis6450 measure (now in mW/m2 by accident)
2026-01-29 Actualizar variables.json 6
2026-01-29 Actualizar variables.json 7
2026-01-29 Pre organizar RECUV 2
2026-01-29 RECUV 2 organizado
2026-01-29 Start farallones TODO trampa
2026-01-29 Finished RECUV 4, TODO organize
2026-02-02 Organized RECUV 4
2026-02-02 Refactor comments and organization in config.h and main.ino for clarity
2026-02-28 Eliminar restrictionssh.yml
2026-02-28 Actualizar variables.json
2026-06-09 Added V3 and GND to CH340
2026-06-09 Reordered USB-C Module and Connections, finished USB-C
2026-06-09 Added CC1 and CC2 resistor
2026-06-09 Added LED, TX and RX to CH340
2026-06-09 Corrected USB-C Resistor
2026-06-09 Corrected V3 PIN for CH340
2026-06-09 Added values for Resistors and Capacitors
2026-06-09 Added UD+ and UD- on CH340
2026-06-09 Added a New RECUV File
    - USB-C Added
    - UD+ and UD- etiquetes added
    - VBUS added
2026-06-09 Added RTS and DTR to CH340
2026-06-09 Added A1117 and GND
2026-06-09 Reorganized and changed 1k by 470 for led intensity
2026-06-09 Finished Bus I2C
2026-06-09 Added all PINs to ESP32S3
2026-06-09 Added CHIP_PU capacitor
2026-06-09 Finished all PCB sections
2026-06-09 Finished Microcontroller section
2026-06-09 added Schottky connection
2026-06-09 Added 3v3 to gnd capacitor for CH340
2026-06-09 Finished Boot Settings
2026-06-09 corrected polygon
2026-06-09 Added voltage divider
2026-06-09 Finished RJ11 sensors and corrected bus i2c bug
2026-06-09 Added VEXT Screw Terminal
2026-06-09 Finished electrical sensors
2026-06-09 Finished PCB
2026-06-09 Finished Power Supply Section
2026-06-09 Added ESP32S3 left row pins
2026-06-09 Closed USB Connector secion
2026-06-09 Corrected PCB Form
2026-06-09 Corrected ESP32 Antenna
